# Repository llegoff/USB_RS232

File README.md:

[:fr:](LISEZMOI.md) [:uk:](README.md)

# USB_RS232

ch340 usb to rs232 PiZero format

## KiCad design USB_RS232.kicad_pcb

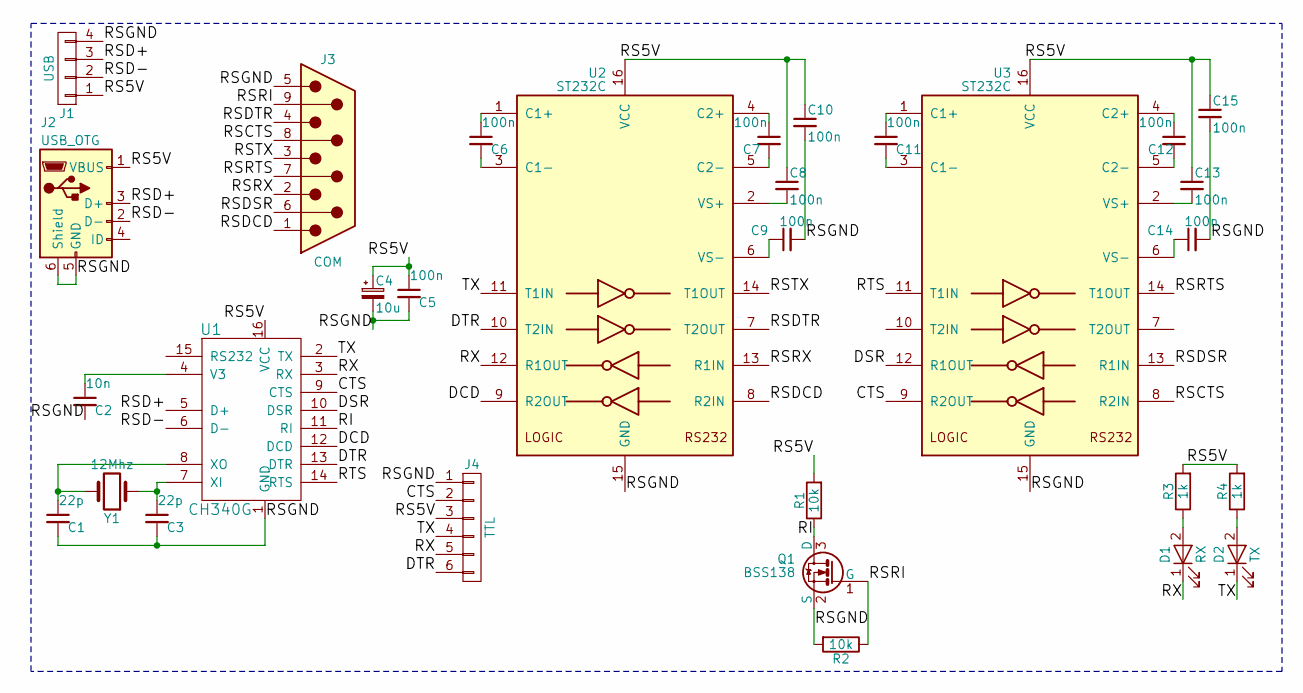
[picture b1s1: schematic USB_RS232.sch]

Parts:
C1, C3: 22p; C_0805
C2: 10n; C_0805
C4: 10u; CP_Elec_4x5.7
C5, C6, C7, C8, C9, C10, C11, C12, C13, C14, C15: 100n; C_0805
D1: RX; LED_0805
D2: TX; LED_0805
J1: USB; Pin_Header_Straight_1x04_Pitch2.54mm
J2: USB_OTG; USB_Mini-B
J3: COM; DB9MC
J4: TTL; Pin_Header_Straight_1x06_Pitch2.54mm
Q1: BSS138; SOT-23
R1, R2: 10k; R_0805
R3, R4: 1k; R_0805
U1: CH340G; SO-16-N
U2, U3: ST232C; SOIC-16_3.9x9.9mm_Pitch1.27mm
Y1: 12Mhz; Crystal_HC49-U_Vertical

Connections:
/CTS: J4.2, U1.9 (CTS), U3.9 (R2OUT)
/DCD: U1.12 (DCD), U2.9 (R2OUT)
/DSR: U1.10 (DSR), U3.12 (R1OUT)
/DTR: J4.6, U1.13 (DTR), U2.10 (T2IN)
/RI: Q1.3 (D), R1.1, U1.11 (RI)
/RS5V: C4.1, C5.1, C8.1, C10.1, C13.1, C15.1, J1.1, J2.1 (VBUS), J4.3, R1.2, R3.2, R4.2, U1.16 (VCC), U2.16 (VCC), U3.16 (VCC)
/RSCTS: J3.8, U3.8 (R2IN)
/RSD+: J1.3, J2.3 (D+), U1.5 (D+)
/RSD-: J1.2, J2.2 (D-), U1.6 (D-)
/RSDCD: J3.1, U2.8 (R2IN)
/RSDSR: J3.6, U3.13 (R1IN)
/RSDTR: J3.4, U2.7 (T2OUT)
/RSGND: C1.2, C2.2, C3.2, C4.2, C5.2, C9.2, C10.2, C14.2, C15.2, J1.4, J2.5 (GND), J2.6 (Shield), J3.5, J4.1, Q1.2 (S), R2.2, U1.1 (GND), U2.15 (GND), U3.15 (GND)
/RSRI: J3.9, Q1.1 (G), R2.1
/RSRTS: J3.7, U3.14 (T1OUT)
/RSRX: J3.2, U2.13 (R1IN)
/RSTX: J3.3, U2.14 (T1OUT)
/RTS: U1.14 (RTS), U3.11 (T1IN)
/RX: D1.1 (K), J4.5, U1.3 (RX), U2.12 (R1OUT)
/TX: D2.1 (K), J4.4, U1.2 (TX), U2.11 (T1IN)
unnamed: C1.1, U1.8 (XO), Y1.2
unnamed: C2.1, U1.4 (V3)
unnamed: C3.1, U1.7 (XI), Y1.1
unnamed: C6.1, U2.1 (C1+)
unnamed: C6.2, U2.3 (C1-)
unnamed: C7.1, U2.4 (C2+)
unnamed: C7.2, U2.5 (C2-)
unnamed: C8.2, U2.2 (VS+)
unnamed: C9.1, U2.6 (VS-)
unnamed: C11.1, U3.1 (C1+)
unnamed: C11.2, U3.3 (C1-)
unnamed: C12.1, U3.4 (C2+)
unnamed: C12.2, U3.5 (C2-)
unnamed: C13.2, U3.2 (VS+)
unnamed: C14.1, U3.6 (VS-)
unnamed: D1.2 (A), R3.1
unnamed: D2.2 (A), R4.1

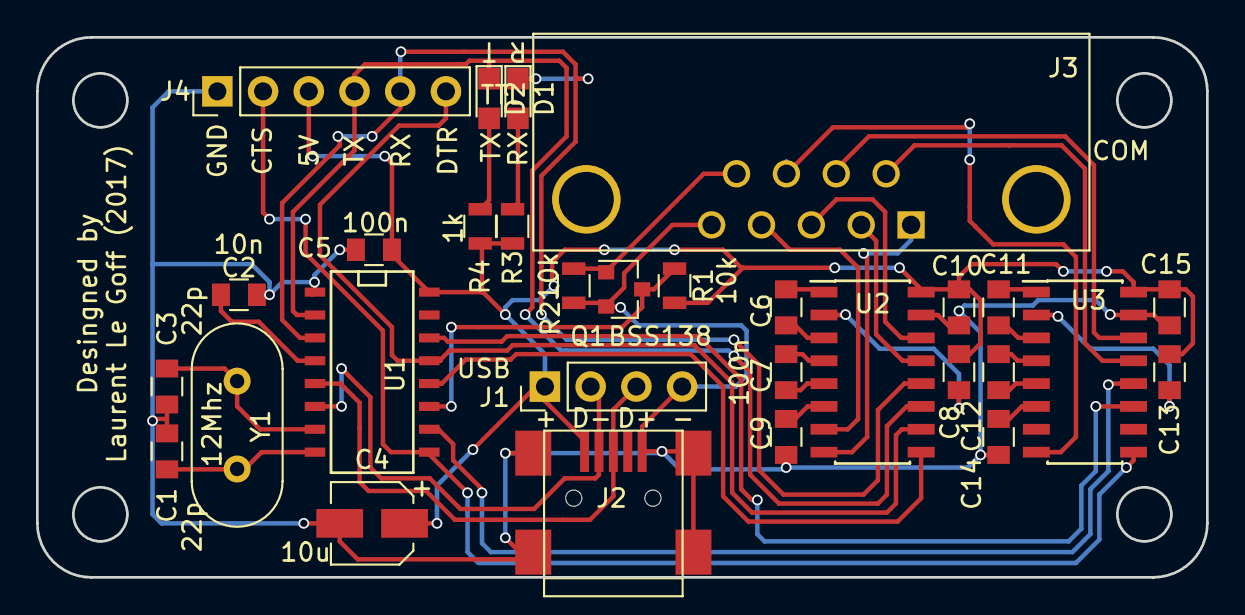
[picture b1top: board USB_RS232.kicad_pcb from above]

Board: 2 copper layers, 65.0 x 30.0 mm, 30 parts (0 on the bottom side), 37 nets.

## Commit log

2017-10-24 Create test
